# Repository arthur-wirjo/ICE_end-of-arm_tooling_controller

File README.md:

# ICE_end-of-arm_tooling_controller: Custom EOAT Servo & IO Interface

A custom-designed, 64mm circular End-of-Arm Tooling (EOAT) controller PCB designed for the Dobot Magician E6 robot arm. It bridges the robot's 24V industrial PNP digital I/O with a custom servo-driven gripper, providing multi-rail power regulation, opto-isolated signal shifting, current sensing, and dual-protocol servo control.

## Overview

The Dobot Magician E6 features an end-effector interface with 24V power and 24V PNP digital I/O (`24V`, `DO_1`, `DO_2`, `DI_1`, `DI_2`, `GND`). To use a custom servo-driven gripper with the arm, I needed an intermediate controller board capable of stepping down the 24V supply and translating the 24V I/O signals into standard hobby PWM or serial bus servo commands.

A major design constraint was the physical footprint: the robot's end-effector is 65mm in diameter. This PCB is designed with a 64mm diameter and matching M6 mounting holes so it can be bolted directly inline between the robot flange and the custom gripper. Additionally, because the board was assembled using a reflow soldering hotplate, the layout was heavily optimized to pack almost all SMD components onto the front side while keeping the footprint compact.

## Key Features

* **Direct Flange Mounting:** 64mm circular PCB profile with M6 mounting holes matching the Dobot Magician E6 end-effector (65mm diameter).
* **Dual Servo Compatibility:** Supports both standard 5V PWM servos (e.g., MG996R) and 12V Half-Duplex UART bus servos (e.g., Feetech ST3215).
* **Multi-Rail Power Regulation:** Dual high-efficiency buck converters stepping 24V down to 12V and 5V for the servos, plus an LDO providing a clean 3.3V rail for logic.
* **Opto-Isolated 24V I/O:** Bidirectional level shifting between the robot's 24V PNP digital I/O (`DI_1`, `DI_2`, `DO_1`, `DO_2`) and the 3.3V MCU logic.
* **Gripper Force / Current Sensing:** Low-side/in-line 50mΩ shunt resistor paired with a 20V/V current sense amplifier to monitor servo load and detect object grip or stall conditions.
* **Reflow-Optimized Layout:** High-density single-sided component placement designed specifically for hotplate reflow assembly.
* **Visual Diagnostics:** Dedicated onboard status LEDs for all power rails (24V, 12V, 5V, 3.3V), optocoupler I/O activity, and MCU heartbeat.

## Hardware

### Computing & Control
* **Microcontroller:** STM32G030F6P6TR (Compact mainstream Arm Cortex-M0+ MCU handling I/O logic, ADC current reading, PWM generation, and half-duplex UART).
* **Supported Actuators:** MG996R (5V + PWM) or Feetech ST3215 (12V + Half-Duplex UART).

### Power Stage & Protection
* **12V & 5V Buck Converters:** 2x TI LMR16030SDDAR (60V, 3A simple switcher buck regulators stepping 24V down to 12V and 5V, paired with 15µH 5A power inductors and SS56 Schottky diodes).
* **3.3V Logic LDO:** Microne ME6211A33PG-N (Steps the 5V rail down to 3.3V for the STM32).
* **Input Protection:** Littelfuse SMBJ26CA Bidirectional TVS Diode (Clamps transient voltage spikes on the 24V robot supply rail).

### Signal Conditioning & Sensing
* **24V I/O Isolation:** 4x Toshiba TLP291(GB-TP,SE) Optocouplers (Translates 24V PNP signals to 3.3V MCU inputs and vice versa).
* **PWM Level Shifter:** TI SN74LVC1T45DBVR Dual-Supply Bus Transceiver (Shifts 3.3V MCU timer output to 5V logic for standard PWM servos).
* **Current Sensing:** FOJAN 50mΩ 1W Shunt Resistor (1206) paired with a TI INA180A1IDBVR Current Sense Amplifier (Gain = 20V/V).

### Connectors & Interface
* **Robot I/O Input:** 6-pin JST-XH SMD (`S6B-XH-SM4-TB`) interfacing with the robot's M8 6-pin aviation connector.
* **UART Servo Output:** 3-pin 2.50mm pitch Molex 5268-03A / `HX25003-3WAP` (For ST3215 serial bus servo).
* **PWM Servo Output:** 3-pin 2.54mm pitch header (`PZ2.54-1x3P`).
* **Debugging:** 5-pin 2.54mm right-angle SMD header (`PZ2.54-1x5P-SMD-RA`) for ST-Link SWD programming.

## Firmware & Control Architecture

The firmware is written in C using the STM32 HAL framework and structured around a deterministic, non-blocking super-loop (`HAL_GetTick()`) without an RTOS to keep flash and RAM overhead minimal on the STM32G030F6P6.

* **50 Hz (20 ms) Control & Current Sensing Task:** Reads opto-isolated Dobot digital outputs, samples and filters servo current via the ADC, and updates either the PWM timer compare register or transmits a Feetech UART packet on state transitions.
* **1 Hz (500 ms toggle) Heartbeat Task:** Blinks the onboard status LED (`PB8`) to confirm normal MCU execution.

### Gripper Control Truth Table

The Dobot's two digital outputs (`DO_1` and `DO_2`) are mapped to four distinct operating modes:

| `D2_OUT` (`PA2`) | `D1_OUT` (`PA1`) | Command Mode | PWM Servo (MG996R) Behavior | UART Servo (Feetech ST3215) Behavior |
| :---: | :---: | :--- | :--- | :--- |
| **LOW (0)** | **LOW (0)** | **Hard Open** | Driven firmly to Open position (`1000 µs`). | Driven to Open position (`1000`) at 80% max torque. |
| **LOW (0)** | **HIGH (1)** | **Hard Close** | Driven firmly to Closed position (`2000 µs`) with 1.2A overload protection. | Driven to Closed position (`3000`) at 80% max torque. |
| **HIGH (1)** | **LOW (0)** | **Soft Open (Free / Idle)** | PWM pulses disabled (`CCR1 = 0`) allowing the gripper fingers to be moved freely by hand. | Torque Enable register (`0x28`) set to `0` so the gripper is back-drivable by hand. |
| **HIGH (1)** | **HIGH (1)** | **Soft Close (Compliant Grip)** | Steps closed incrementally and locks position with a slight back-off as soon as current reaches `450 mA`. | Commands Close with internal torque limit throttled to 25% (`Reg 0x30 = 250`) and reduced speed. |

### Current Sensing & Cable Protection
With a **50 mΩ** sense resistor and a **20 V/V** amplifier gain (`INA180A1`), the analog output scales cleanly to **1.0 V/A** (**1 mV = 1 mA**). Raw 12-bit ADC readings are smoothed using a fast integer exponential moving average filter:
```c
g_servo_current_mA = ((3 * g_servo_current_mA) + current_mA) >> 2;
```
To protect the robot's 1.5A-rated M8 aviation cable and prevent servo burn-out under stall conditions, the firmware enforces a **450 mA** threshold for compliant soft gripping and a **1200 mA (1.2A)** hard overload cutoff.

### MCU Pinout & STM32CubeMX Configuration

* **System Clock:** 64 MHz (Internal HSI + PLL)

| Pin | Signal / Label | Peripheral Mode | Key Configuration Parameters |
| :--- | :--- | :--- | :--- |
| `PA1` | `D1_OUT` | `GPIO_Input` | Active-High (External 10kΩ pull-down on PCB), `GPIO_NOPULL` |
| `PA2` | `D2_OUT` | `GPIO_Input` | Active-High (External 10kΩ pull-down on PCB), `GPIO_NOPULL` |
| `PA3` | `D1_IN` | `GPIO_Output` | Push-Pull, Active-High optocoupler drive to robot `DI_1` |
| `PA4` | `D2_IN` | `GPIO_Output` | Push-Pull, Active-High optocoupler drive to robot `DI_2` |
| `PA6` | `PWM_SERVO` | `TIM3_CH1` | Prescaler = `63` (1 MHz / 1 µs tick), Period = `19999` (50 Hz / 20 ms) |
| `PA7` | `CURR_SENSE` | `ADC1_IN7` | 12-bit resolution, `PCLK/4`, `79.5 Cycles` sampling time, calibrated on boot |
| `PB6` | `UART_SERVO` | `USART1_TX` | Half-Duplex Single-Wire mode, `1,000,000` bps (1 Mbps), 8N1 |
| `PB8` | `HEARTBEAT` | `GPIO_Output` | Push-Pull status LED, toggled every 500 ms |
| `PA13` | `SYS_SWDIO` | `SYS` | Serial Wire Debug Data |
| `PA14` | `SYS_SWCLK` | `SYS` | Serial Wire Debug Clock |

## Current Status

* **V1.0 (Completed & Operational):** Hardware bring-up, STM32G0 firmware development, and full integration testing with the Dobot Magician E6 robot arm and gripper are complete. All power rails (12V, 5V, 3.3V), opto-isolated 24V I/O channels, current sensing feedback, and servo control modes operated as designed on the first test run.
* **Future Enhancements:** Implement outbound digital feedback (`D1_IN`, `D2_IN`) to report object grip detection and fault/stall states back to the Dobot controller.

## Project Timeline

| Date | Milestone |
|---|---|
| Nov 4, 2026 | Project planning and component research |
| Nov 5, 2026 | Started schematic capture |
| Nov 6, 2026 | Schematic completed; started 64mm circular PCB layout |
| Nov 7, 2026 | PCB layout completed; PCBs and BOM ordered |
| Nov 14, 2026 | PCB and components arrived |
| Nov 15, 2026 | PCB soldered |
| Nov 20, 2026 | STM32 Firmware written; PCB tested and working with robot arm |

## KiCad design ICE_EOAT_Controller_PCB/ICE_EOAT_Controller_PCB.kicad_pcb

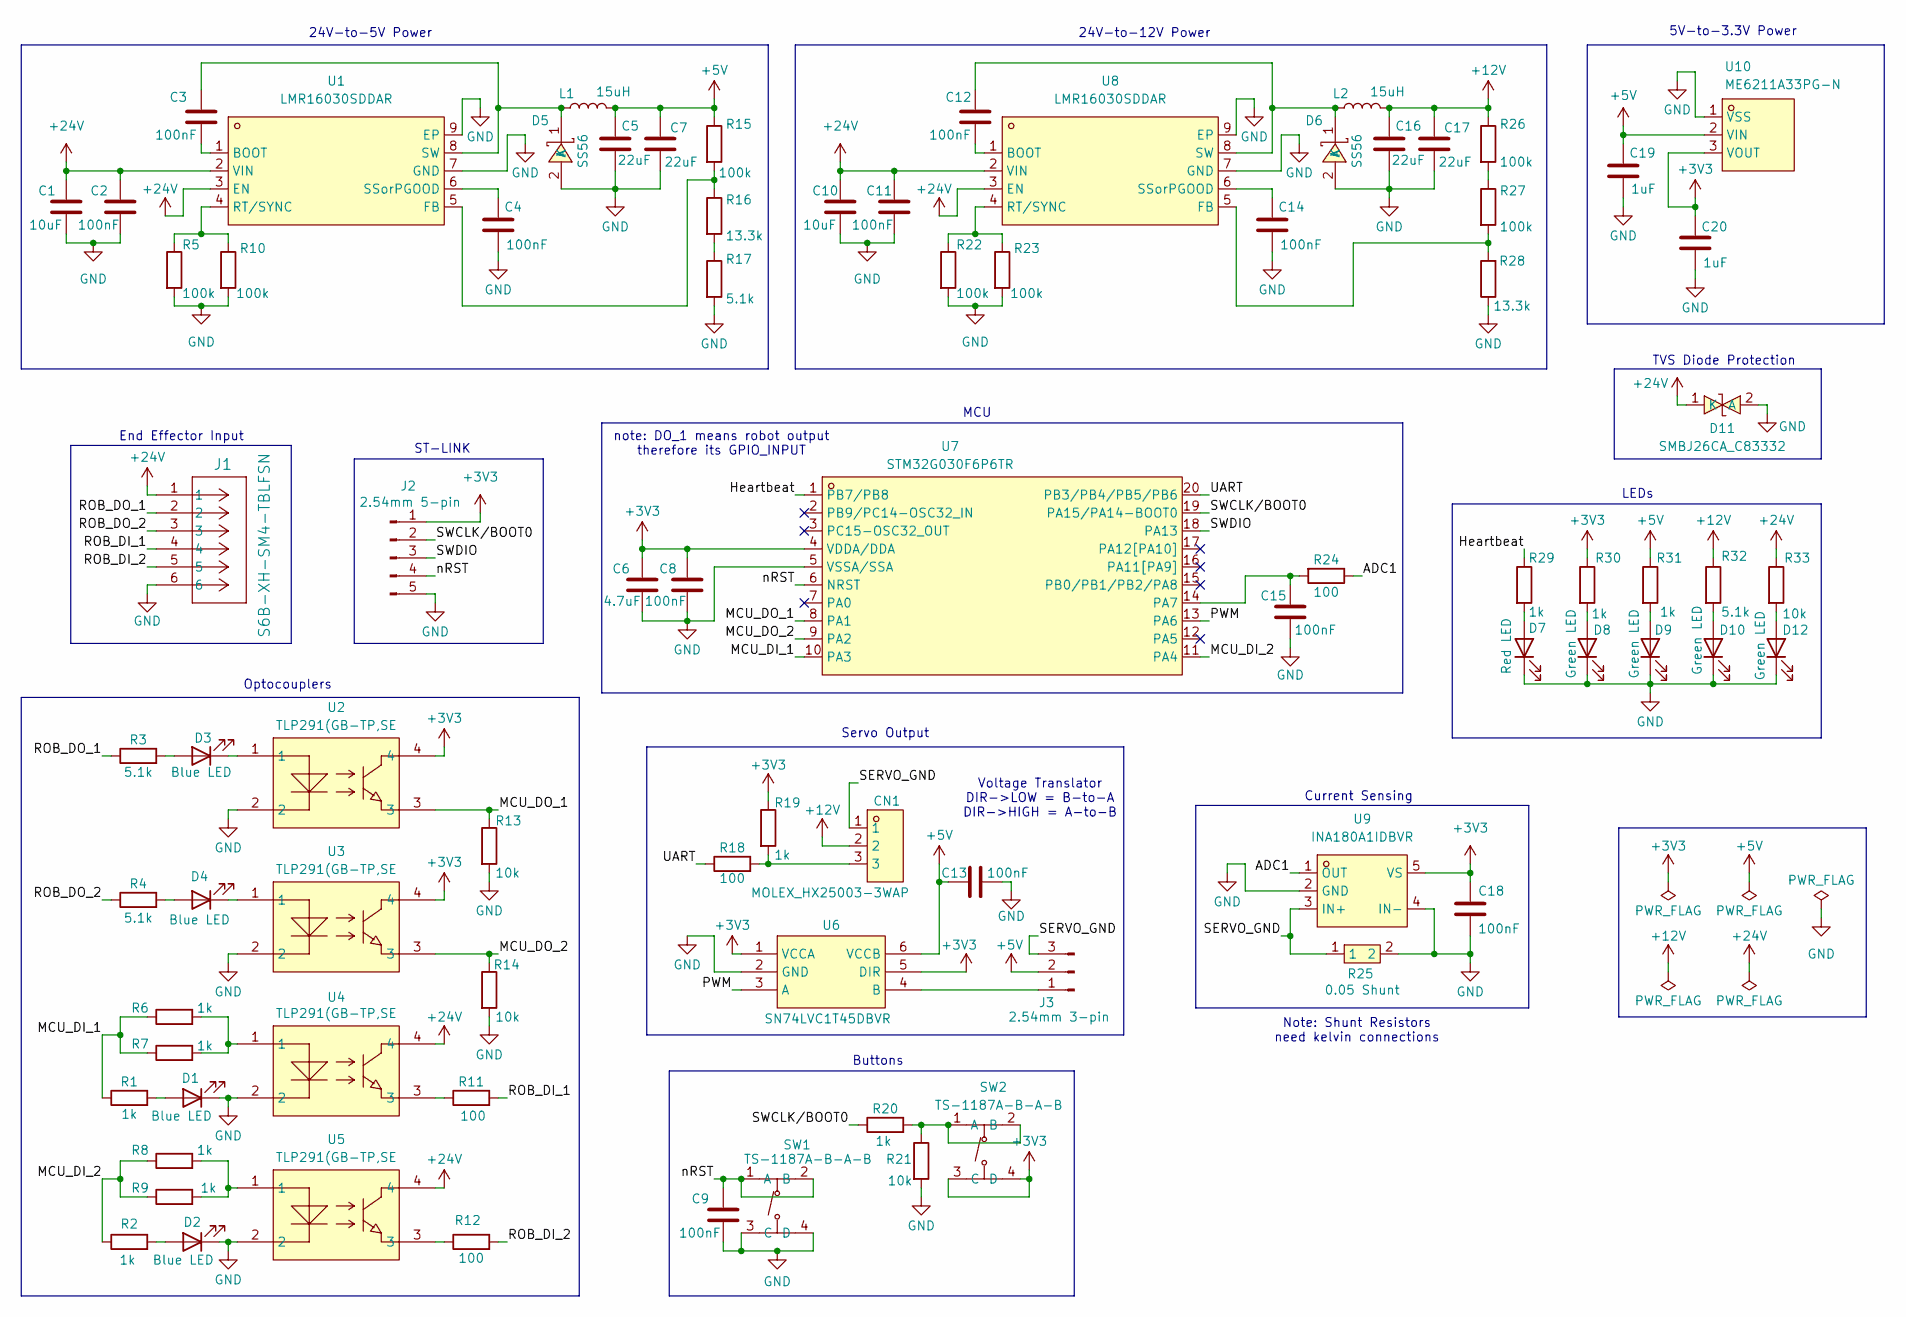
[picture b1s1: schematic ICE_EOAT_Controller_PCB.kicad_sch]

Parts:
C1, C10: 10uF; C_1206_3216Metric_Pad1.33x1.80mm_HandSolder
C2, C3, C4, C8, C9, C11, C12, C13, C14, C15, C18: 100nF; C_0603_1608Metric_Pad1.08x0.95mm_HandSolder
C5, C7, C16, C17: 22uF; C_1206_3216Metric_Pad1.33x1.80mm_HandSolder
C6: 4.7uF; C_0805_2012Metric_Pad1.18x1.45mm_HandSolder
C19, C20: 1uF; C_0603_1608Metric_Pad1.08x0.95mm_HandSolder
CN1: MOLEX_HX25003-3WAP; MOLEX_CONN-TH_3P-P2.50_HX25003-3WAP; MPN HX25003-3WAP; LCSC Part C442327
D1, D2, D3, D4: Blue LED; LED_0603_1608Metric_Pad1.05x0.95mm_HandSolder
D5, D6: SS56; Schottky_SMA_L4.3-W2.6-LS5.2-RD; MPN SS56; LCSC Part C65009
D7: Red LED; LED_0603_1608Metric_Pad1.05x0.95mm_HandSolder
D8, D9, D10, D12: Green LED; LED_0603_1608Metric_Pad1.05x0.95mm_HandSolder
D11: SMBJ26CA_C83332; TVS_SMB_L4.6-W3.6-LS5.3-BI; MPN SMBJ26CA; LCSC Part C83332
J1: S6B-XH-SM4-TBLFSN; JST_XH_CONN_S6B-XH-SM4-TB_JST
J2: 2.54mm 5-pin; PinHeader_1x05_P2.54mm_Horizontal
J3: 2.54mm 3-pin; PinHeader_1x03_P2.54mm_Horizontal
L1, L2: 15uH; INDUCTOR_IND-SMD_L7.6-W7.0
R1, R2, R6, R7, R8, R9, R19, R20, R29, R30, R31: 1k; R_0603_1608Metric_Pad0.98x0.95mm_HandSolder
R3, R4, R17, R32: 5.1k; R_0805_2012Metric_Pad1.20x1.40mm_HandSolder
R5, R10, R15, R22, R23, R26, R27: 100k; R_0603_1608Metric_Pad0.98x0.95mm_HandSolder
R11, R12, R18, R24: 100; R_0603_1608Metric_Pad0.98x0.95mm_HandSolder
R13, R14, R21, R33: 10k; R_0603_1608Metric_Pad0.98x0.95mm_HandSolder
R16, R28: 13.3k; R_0603_1608Metric_Pad0.98x0.95mm_HandSolder
R25: 0.05 Shunt; Shunt_R1206; MPN FRM121WFR050TM; LCSC Part C7467249
SW1, SW2: TS-1187A-B-A-B; BUTTON_SW-SMD_4P-L5.1-W5.1-P3.70-LS6.5-TL_H1.5; MPN TS-1187A-B-A-B; LCSC Part C318884
U1, U8: LMR16030SDDAR; BUCK_SOIC-8_L4.9-W3.9-P1.27-LS6.0-BL-EP2.3; MPN LMR16030SDDAR; LCSC Part C136648
U2, U3, U4, U5: TLP291(GB-TP,SE; Optocoupler_SOP-4_L4.4-W2.8-P1.27-LS7.0-BR; MPN TLP291(GB-TP,SE; LCSC Part C55144
U6: SN74LVC1T45DBVR; Voltage_Translator_SOT-23-6_L2.9-W1.6-P0.95-LS2.8-BR; MPN SN74LVC1T45DBVR; LCSC Part C7843
U7: STM32G030F6P6TR; MCU_TSSOP-20_L6.5-W4.4-P0.65-LS6.4-BL; MPN STM32G030F6P6TR; LCSC Part C529330
U9: INA180A1IDBVR; Amplifier_SOT-23-5_L3.0-W1.7-P0.95-LS2.8-BR; MPN INA180A1IDBVR; LCSC Part C122228
U10: ME6211A33PG-N; LDO_SOT-89_L4.5-W2.5-P1.50-LS4.2-BR; MPN ME6211A33PG-N; LCSC Part C236673

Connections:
+3V3: C6.1, C8.1, C18.1, C20.1, J2.1, R19.1, R30.1, SW2.3 (C), SW2.4 (D), U2.4, U3.4, U6.1 (VCCA), U6.5 (DIR), U7.4 (VDDA/DDA), U9.5 (VS), U10.3 (VOUT)
+5V: C5.1, C7.1, C13.1, C19.1, J3.2, L1.2, R15.1, R31.1, U6.6 (VCCB), U10.2 (VIN)
+12V: C16.1, C17.1, CN1.2, L2.2, R26.1, R32.1
+24V: C1.1, C2.1, C10.1, C11.1, D11.1 (K), J1.1, R33.1, U1.2 (VIN), U1.3 (EN), U4.4, U5.4, U8.2 (VIN), U8.3 (EN)
/ADC1: R24.1, U9.1 (OUT)
/Heartbeat: R29.1, U7.1 (PB7/PB8)
/MCU_DI_1: R1.1, R6.1, R7.1, U7.10 (PA3)
/MCU_DI_2: R2.1, R8.1, R9.1, U7.11 (PA4)
/MCU_DO_1: R13.1, U2.3, U7.8 (PA1)
/MCU_DO_2: R14.1, U3.3, U7.9 (PA2)
/PWM: U6.3 (A), U7.13 (PA6)
/ROB_DI_1: J1.4, R11.2
/ROB_DI_2: J1.5, R12.2
/ROB_DO_1: J1.2, R3.1
/ROB_DO_2: J1.3, R4.1
/SERVO_GND: CN1.1, J3.3, R25.1, U9.3 (IN+)
/SWCLK/BOOT0: J2.2, R20.1, U7.19 (PA15/PA14-BOOT0)
/SWDIO: J2.3, U7.18 (PA13)
/UART: R18.1, U7.20 (PB3/PB4/PB5/PB6)
/nRST: C9.1, J2.4, SW1.1 (A), SW1.2 (B), U7.6 (NRST)
GND: C1.2, C2.2, C4.2, C5.2, C6.2, C7.2, C8.2, C9.2, C10.2, C11.2, C13.2, C14.2, C15.2, C16.2, C17.2, C18.2, C19.2, C20.2, D1.1 (K), D2.1 (K), D5.2 (A), D6.2 (A), D7.1 (K), D8.1 (K), D9.1 (K), D10.1 (K), D11.2 (A), D12.1 (K), J1.6, J1.7, J1.8, J2.5, R5.2, R10.2, R13.2, R14.2, R17.2, R21.2, R22.2, R23.2, R25.2, R28.1, SW1.3 (C), SW1.4 (D), U1.7 (GND), U1.9 (EP), U2.2, U3.2, U4.2, U5.2, U6.2 (GND), U7.5 (VSSA/SSA), U8.7 (GND), U8.9 (EP), U9.2 (GND), U9.4 (IN-), U10.1 (VSS)
unnamed: CN1.3, R18.2, R19.2
unnamed: D1.2 (A), R1.2
unnamed: D2.2 (A), R2.2
unnamed: D3.2 (A), R3.2
unnamed: D3.1 (K), U2.1
unnamed: D4.2 (A), R4.2
unnamed: D4.1 (K), U3.1
unnamed: C3.1, D5.1 (K), L1.1, U1.8 (SW)
unnamed: C12.1, D6.1 (K), L2.1, U8.8 (SW)
unnamed: D7.2 (A), R29.2
unnamed: D8.2 (A), R30.2
unnamed: D9.2 (A), R31.2
unnamed: D10.2 (A), R32.2
unnamed: D12.2 (A), R33.2
unnamed: J3.1, U6.4 (B)
unnamed: R6.2, R7.2, U4.1
unnamed: R8.2, R9.2, U5.1
unnamed: R11.1, U4.3
unnamed: R12.1, U5.3
unnamed: R16.2, R17.1
unnamed: R26.2, R27.1
unnamed: R20.2, R21.1, SW2.1 (A), SW2.2 (B)
unnamed: C3.2, U1.1 (BOOT)
unnamed: R15.2, R16.1, U1.5 (FB)
unnamed: R5.1, R10.1, U1.4 (RT/SYNC)
unnamed: C4.1, U1.6 (SSorPGOOD)
unnamed: C15.1, R24.2, U7.14 (PA7)
unnamed: C12.2, U8.1 (BOOT)
unnamed: R27.2, R28.2, U8.5 (FB)
unnamed: R22.1, R23.1, U8.4 (RT/SYNC)
unnamed: C14.1, U8.6 (SSorPGOOD)

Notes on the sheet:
Voltage Translator DIR->LOW = B-to-A DIR->HIGH = A-to-B
TVS Diode Protection
ST-LINK
Buttons
MCU
note: DO_1 means robot output therefore its GPIO_INPUT
Optocouplers
5V-to-3.3V Power
End Effector Input
Servo Output
LEDs
Note: Shunt Resistors need kelvin connections
24V-to-5V Power
24V-to-12V Power
Current Sensing

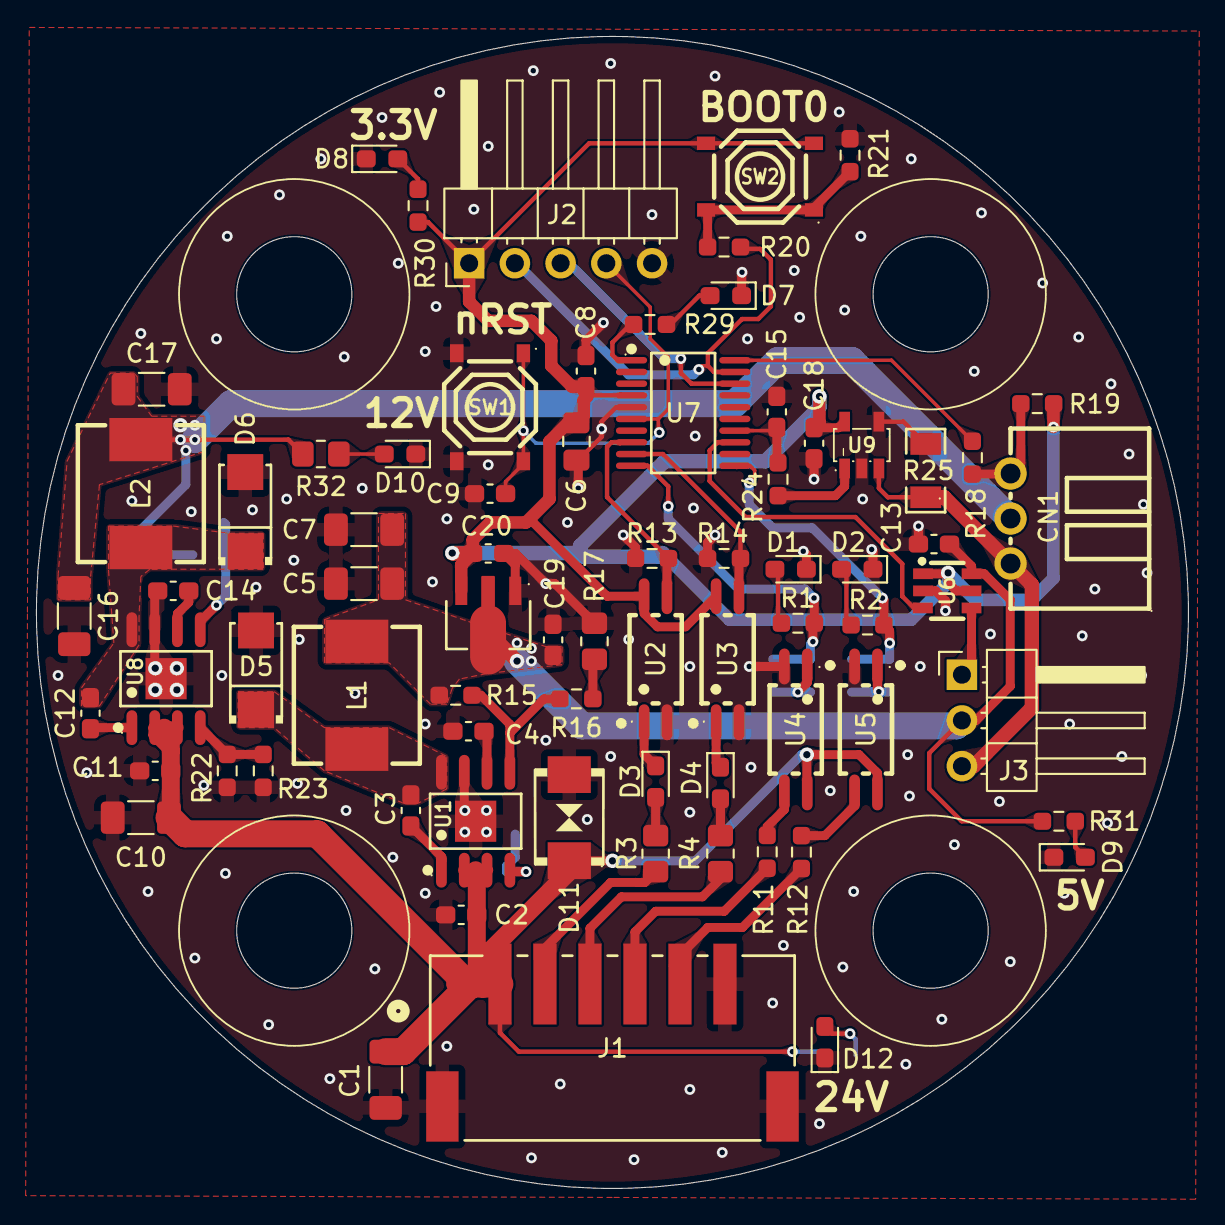
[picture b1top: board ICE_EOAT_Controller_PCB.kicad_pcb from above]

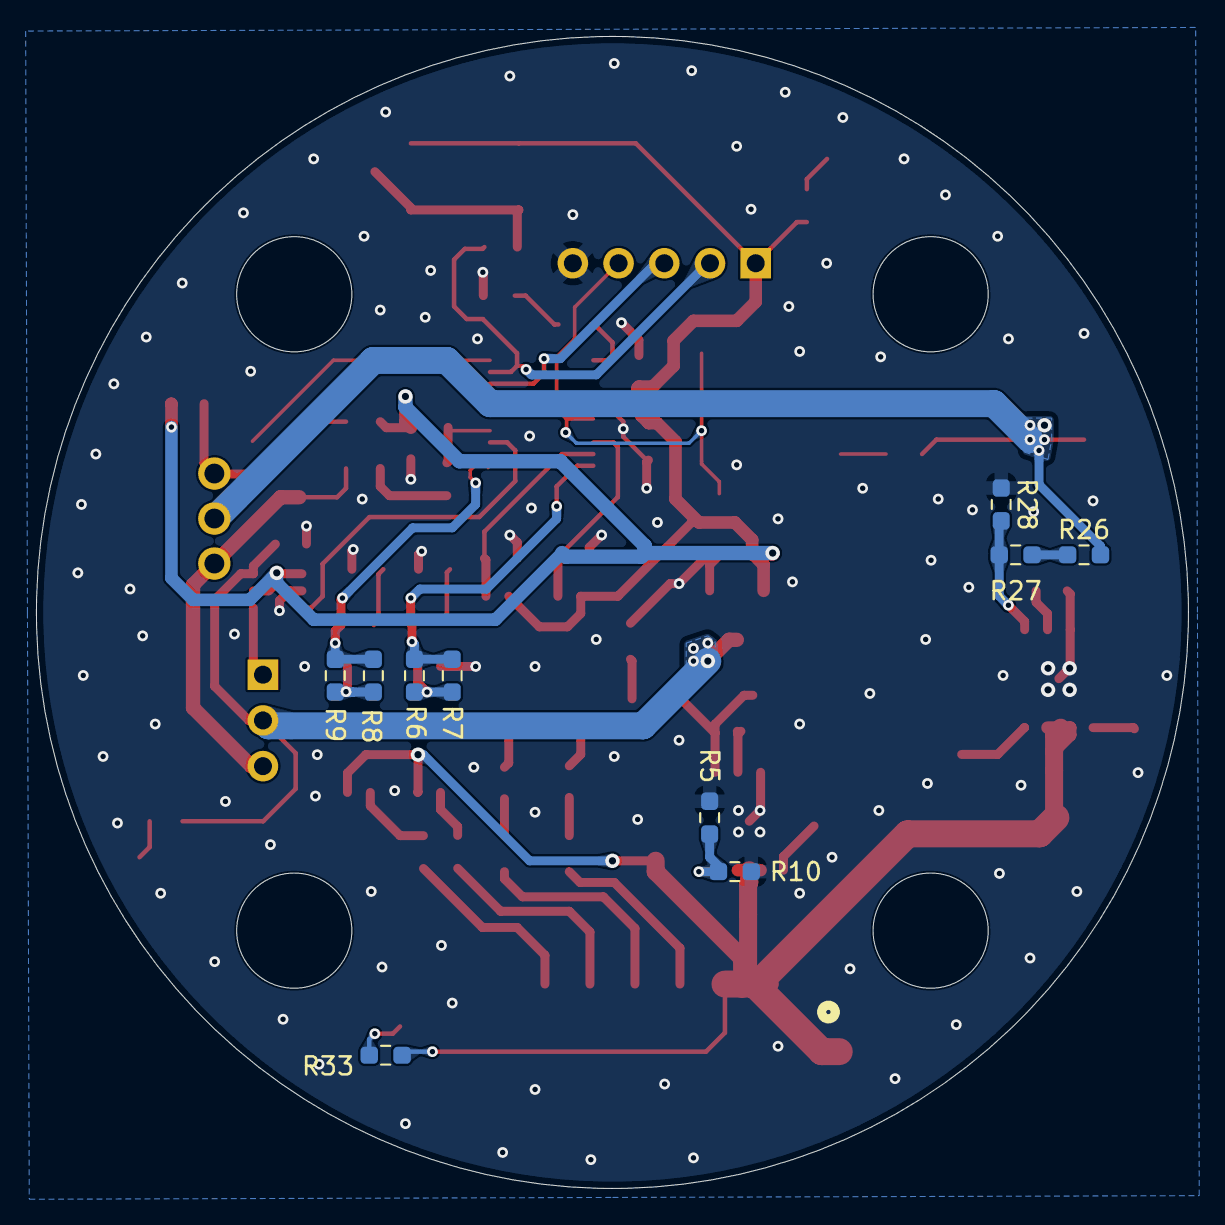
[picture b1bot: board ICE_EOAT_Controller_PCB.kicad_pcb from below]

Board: 4 copper layers, 64.0 x 64.0 mm, 83 parts (10 on the bottom side), 52 nets.

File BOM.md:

### EOAT Controller Board BOM

| Category | Description / Value | Manufacturer & Part Number | LCSC / Part ID | Designator | Qty |
| :--- | :--- | :--- | :--- | :--- | :--- |
| **Resistors** | 100Ω, 0603, 1%, 100mW | FOJAN FRC0603F1000TS | C2906981 | R11, R12, R18, R24 | 4 |
| | 1kΩ, 0603, 1%, 100mW | FOJAN FRC0603F1001TS | C2907002 | R1, R2, R6–R9, R19, R20, R29–R31 | 11 |
| | 5.1kΩ, 0805, 1%, 125mW | FOJAN FRC0805F5101TS | C2907269 | R3, R4, R17, R32 | 4 |
| | 10kΩ, 0603, 1%, 100mW | FOJAN FRC0603F1002TS | C2906982 | R13, R14, R21, R33 | 4 |
| | 13.3kΩ, 0603, 1%, 100mW | FOJAN FRC0603F1332TS | C2933140 | R16, R28 | 2 |
| | 100kΩ, 0603, 1%, 100mW | FOJAN FRC0603F1003TS | C2906980 | R5, R10, R15, R22, R23, R26, R27 | 7 |
| | 0.05Ω, 1206, 1%, 1W (Shunt) | FOJAN FRM121WFR050TM | C7467249 | R25 | 1 |
| **Capacitors** | 100nF, 0603, 50V, X7R, 10% | FOJAN FCC0603B104K500CT | C5137636 | C2–C4, C8, C9, C11–C15, C18 | 11 |
| | 1uF, 0603, 25V, X7R, 10% | Samsung Electro-Mechanics CL10B105KA8NNNC | C29936 | C19, C20 | 2 |
| | 4.7uF, 0805, 25V, X7R, 10% | Samsung Electro-Mechanics CL21B475KAFNNNE | C98195 | C6 | 1 |
| | 10uF, 1206, 50V, X7R, 10% | Samsung Electro-Mechanics CL31B106KBHNNNE | C89632 | C1, C10 | 2 |
| | 22uF, 1206, 35V, X5R, 20% | FOJAN FCC1206X226M350HT | C46635923 | C5, C7, C16, C17 | 4 |
| **Inductors** | 15uH, 7.5x6.8mm, 5A, 5.5A (Isat), 54mΩ | FANGCHENG FCH0650-150M | C20415538 | L1, L2 | 2 |
| **Diodes & LEDs** | TVS Diode, Bidirectional, VRWM=26V, Vc=42.1V | Littelfuse SMBJ26CA | C83332 | D11 | 1 |
| | Schottky Diode, 60V, 5A | MDD SS56 | C65009 | D5, D6 | 2 |
| | Red LED, 0603, Vf=2.3V, 20mA, 225mcd | XINGLIGHT XL-1608SURC-06 | C965799 | D7 | 1 |
| | Green LED, 0603, Vf=2.7~3.2V, 25mA, 358mcd | YONGYUTAI YLED0603G | C19273151 | D8, D9, D10, D12 | 4 |
| | Blue LED, 0603, Vf=2.6~3.3V, 5mA, 300mcd | XINGLIGHT XL-1608UBC-06A | C7371904 | D1, D2, D3, D4 | 4 |
| **ICs** | Microcontroller | ST STM32G030F6P6TR | C529330 | U7 | 1 |
| | Buck Converter | TI LMR16030SDDAR | C136648 | U1, U8 | 2 |
| | LDO | MICRONE ME6211A33PG-N | C236673 | U10 | 1 |
| | Optocoupler | TOSHIBA TLP291(GB-TP,SE) | C55144 | U2, U3, U4, U5 | 4 |
| | Voltage Translator | TI SN74LVC1T45DBVR | C7843 | U6 | 1 |
| | Current Sense Amplifier | TI INA180A1IDBVR | C122228 | U9 | 1 |
| **Connectors** | JST-XH 6-pin | JST S6B-XH-SM4-TB(LF)(SN) | - | - | 1 |
| | ST-Link 2.54mm 5-pin | 1x5P 2.54mm Pin Header | - | - | 1 |
| | PWM Servo Output 2.54mm 3-pin | 1x3P 2.54mm Pin Header | - | - | 1 |
| | Digital Servo Output Molex 3-pin | Hongxing HX25003-3WAP | C442327 | - | 1 |
| **Switches** | MCU nRST and BOOT0 Tactile Buttons | XKB Connection TS-1187A-B-A-B | C318884 | - | 2 |

### Off-Board Components (Cables)

| Category | Description / Value | Qty |
| :--- | :--- | :--- |
| **Cables** | M8 6-pin Male Aviation Connector Cable | 1 |
| | XH 2.54mm pitch single-sided, 22AWG Cable | 1 |

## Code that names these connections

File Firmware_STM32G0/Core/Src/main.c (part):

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
/* USER CODE BEGIN PV */
typedef enum {
    SERVO_TYPE_PWM = 0,     // MG996R (5V PWM on PA6)
    SERVO_TYPE_UART = 1     // Feetech ST3215 (12V Half-Duplex UART on PB6)
} ServoType_t;

typedef enum {
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/* USER CODE BEGIN 0 */

// ======================= HELPER FUNCTIONS ====================================
// PA7 -> ADC1_IN7, Shunt = 50mOhm, Amplifier Gain = 20V/V -> 1.0V/A
uint32_t Read_Servo_Current_mA(void) {
  HAL_ADC_Start(&hadc1);
  if (HAL_ADC_PollForConversion(&hadc1, 5) == HAL_OK) {
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  // ================ INITIALIZATION ===================
  // Calibrate ADC on startup for accurate current sensing
  HAL_ADCEx_Calibration_Start(&hadc1);
  // start PWM timer on PA6 (TIM3_CH1) with pulse = 0 (idle/free on boot)
  __HAL_TIM_SET_COMPARE(&htim3, TIM_CHANNEL_1, 0);
  HAL_TIM_PWM_Start(&htim3, TIM_CHANNEL_1);
  uint32_t last_control_tick = 0;
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      last_control_tick = now;
      
      // Read Dobot Inputs (Active-HIGH via optocouplers)
      // (D1_O -> PA1), (D2_O -> PA2)
      uint8_t d1_output; 
      if (HAL_GPIO_ReadPin(GPIOA, GPIO_PIN_1) == GPIO_PIN_SET) {
        d1_output = 1;
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      g_last_cmd = g_current_cmd;
    }

    // 1Hz (500ms) HEARTBEAT LED Task (PB8)
    if (now - last_heartbeat_tick >= 500) {
      last_heartbeat_tick = now;
      HAL_GPIO_TogglePin(GPIOB, GPIO_PIN_8);
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  __HAL_RCC_GPIOA_CLK_ENABLE();

  /*Configure GPIO pin Output Level */
  HAL_GPIO_WritePin(HEARTBEAT_GPIO_Port, HEARTBEAT_Pin, GPIO_PIN_RESET);

  /*Configure GPIO pin Output Level */
  HAL_GPIO_WritePin(GPIOA, D1_IN_Pin|D2_IN_Pin, GPIO_PIN_RESET);

  /*Configure GPIO pin : HEARTBEAT_Pin */
  GPIO_InitStruct.Pin = HEARTBEAT_Pin;
  GPIO_InitStruct.Mode = GPIO_MODE_OUTPUT_PP;
  GPIO_InitStruct.Pull = GPIO_NOPULL;
  GPIO_InitStruct.Speed = GPIO_SPEED_FREQ_LOW;
  HAL_GPIO_Init(HEARTBEAT_GPIO_Port, &GPIO_InitStruct);

  /*Configure GPIO pins : D1_OUT_Pin D2_OUT_Pin */
  GPIO_InitStruct.Pin = D1_OUT_Pin|D2_OUT_Pin;
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

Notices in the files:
Firmware_STM32G0/Core/Src/main.c:
Copyright (c) 2026 STMicroelectronics.
All rights reserved.
This software is licensed under terms that can be found in the LICENSE file
